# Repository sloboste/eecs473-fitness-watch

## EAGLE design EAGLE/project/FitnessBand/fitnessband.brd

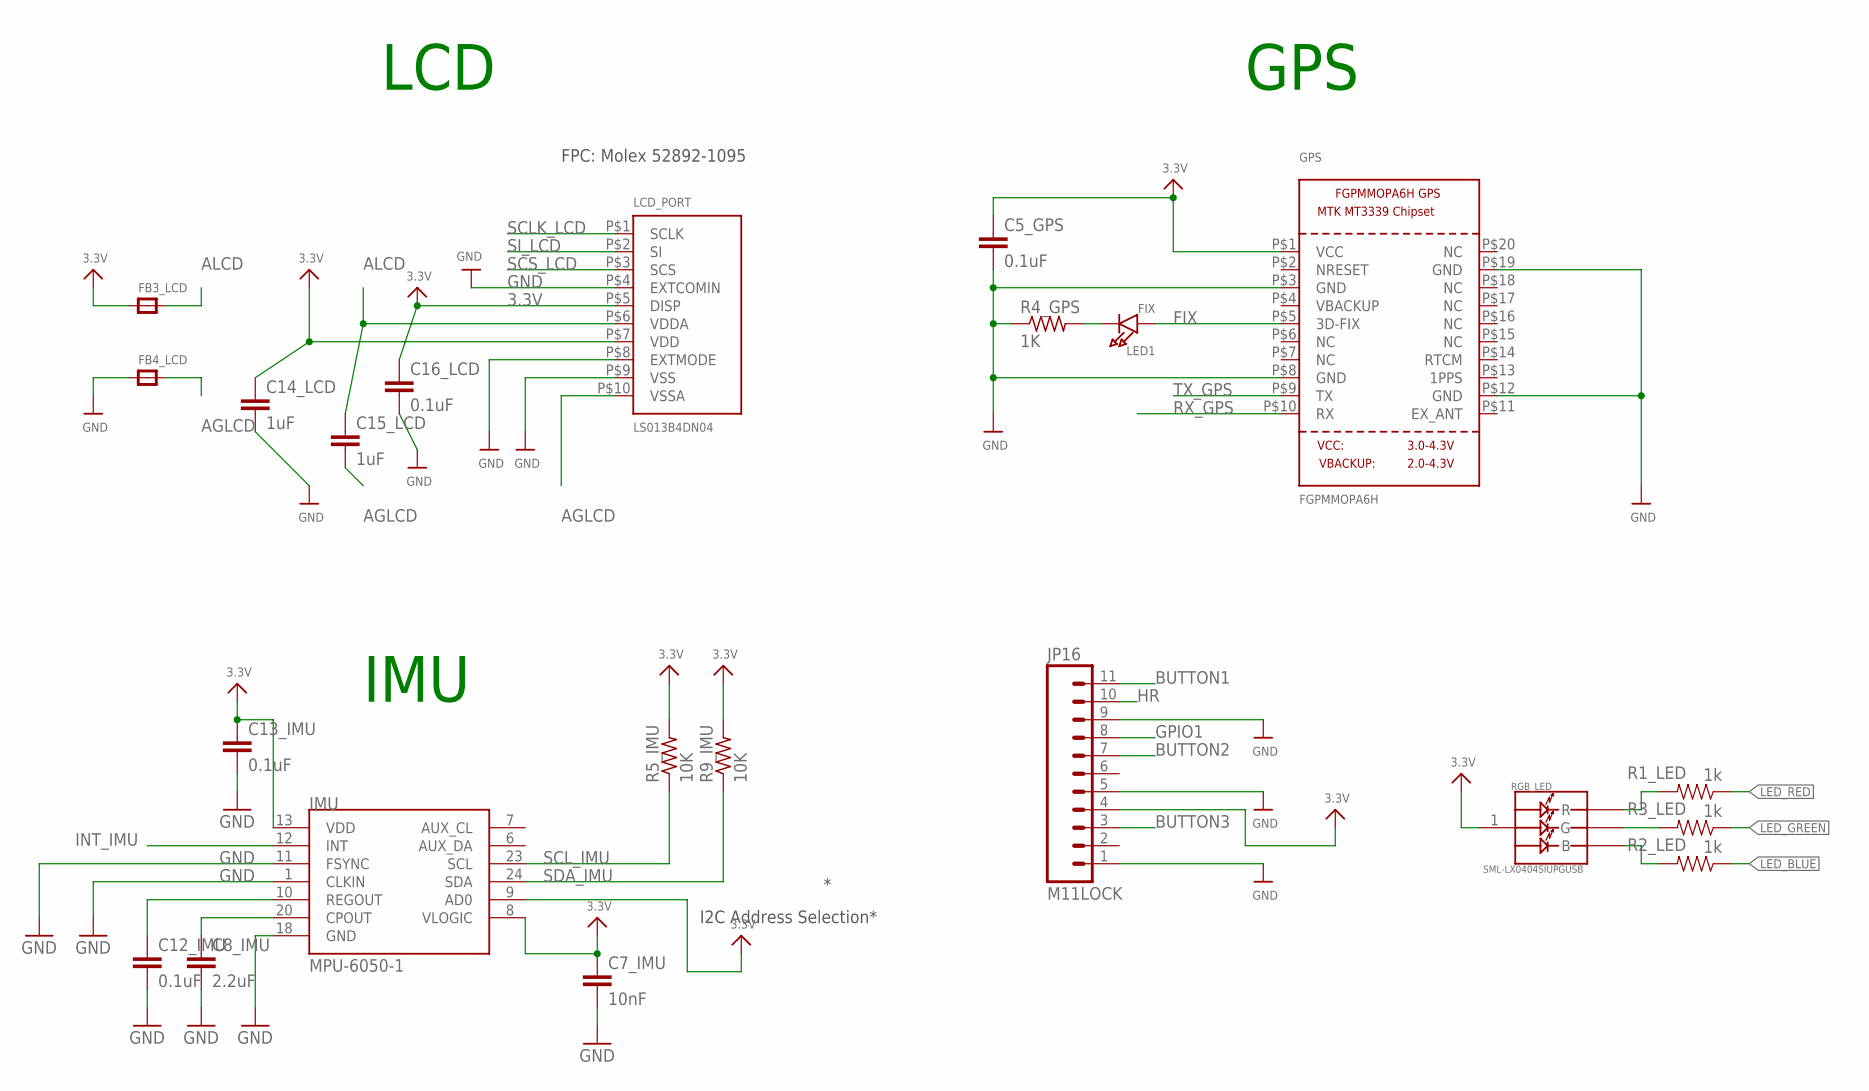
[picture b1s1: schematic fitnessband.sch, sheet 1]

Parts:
C5_GPS, C12_IMU, C13_IMU, C16_LCD: 0.1uF; C0402
C7_IMU: 10nF; C0402
C8_IMU: 2.2uF; C0402
C14_LCD, C15_LCD: 1uF; C0402
FB3_LCD, FB4_LCD: FERRITE_0805; _0805
GPS: FGPMMOPA6H
IMU: MPU-6050-1; QFN-24-4MM2
JP16: M11LOCK; 1X11_LOCK
LCD_PORT: LS013B4DN04; FPC_10PIN_52892-1095
LED1: FIX; CHIPLED_0805
R1_LED, R2_LED, R3_LED: 1k; 0402_RES
R4_GPS: 1K; R0402
R5_IMU, R9_IMU: 10K; R0402
RGB_LED: SML-LX0404SIUPGUSB; 1MM_SQ_4PAD

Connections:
3.3V: C5_GPS.1, C7_IMU.1, C13_IMU.1, C14_LCD.1, C16_LCD.1, FB3_LCD.1, GPS.P$1 (VCC), IMU.8 (VLOGIC), IMU.9 (AD0), IMU.13 (VDD), JP16.4, LCD_PORT.P$5 (DISP), LCD_PORT.P$7 (VDD), R5_IMU.2, R9_IMU.2, RGB_LED.1 (VDD); also elsewhere on the board
AGLCD: C15_LCD.2, FB4_LCD.2, LCD_PORT.P$10 (VSSA)
ALCD: C15_LCD.1, FB3_LCD.2, LCD_PORT.P$6 (VDDA)
BUTTON1: JP16.11; also elsewhere on the board
BUTTON2: JP16.7; also elsewhere on the board
BUTTON3: JP16.3; also elsewhere on the board
FIX: GPS.P$5 (3D-FIX), LED1.A
GND: C5_GPS.2, C7_IMU.2, C8_IMU.2, C12_IMU.2, C13_IMU.2, C14_LCD.2, C16_LCD.2, FB4_LCD.1, GPS.P$3 (GND), GPS.P$8 (GND), GPS.P$12 (GND), GPS.P$19 (GND), IMU.1 (CLKIN), IMU.11 (FSYNC), IMU.18 (GND), JP16.1, JP16.5, JP16.9, LCD_PORT.P$4 (EXTCOMIN), LCD_PORT.P$8 (EXTMODE), LCD_PORT.P$9 (VSS), R4_GPS.1; also elsewhere on the board
GPIO1: JP16.8; also elsewhere on the board
HR: JP16.10; also elsewhere on the board
INT_IMU: IMU.12 (INT); also elsewhere on the board
LED_BLUE: R2_LED.1; also elsewhere on the board
LED_GREEN: R3_LED.1; also elsewhere on the board
LED_RED: R1_LED.1; also elsewhere on the board
unnamed: R1_LED.2, RGB_LED.2 (R)
unnamed: R3_LED.2, RGB_LED.4 (G)
unnamed: R2_LED.2, RGB_LED.3 (B)
unnamed: LED1.C, R4_GPS.2
unnamed: C8_IMU.1, IMU.20 (CPOUT)
unnamed: C12_IMU.1, IMU.10 (REGOUT)
RX_GPS: GPS.P$10 (RX); also elsewhere on the board
SCLK_LCD: LCD_PORT.P$1 (SCLK); also elsewhere on the board
SCL_IMU: IMU.23 (SCL), R5_IMU.1; also elsewhere on the board
SCS_LCD: LCD_PORT.P$3 (SCS); also elsewhere on the board
SDA_IMU: IMU.24 (SDA), R9_IMU.1; also elsewhere on the board
SI_LCD: LCD_PORT.P$2 (SI); also elsewhere on the board
TX_GPS: GPS.P$9 (TX); also elsewhere on the board

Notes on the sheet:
FPC: Molex 52892-1095
LCD
GPS
I2C Address Selection*
IMU

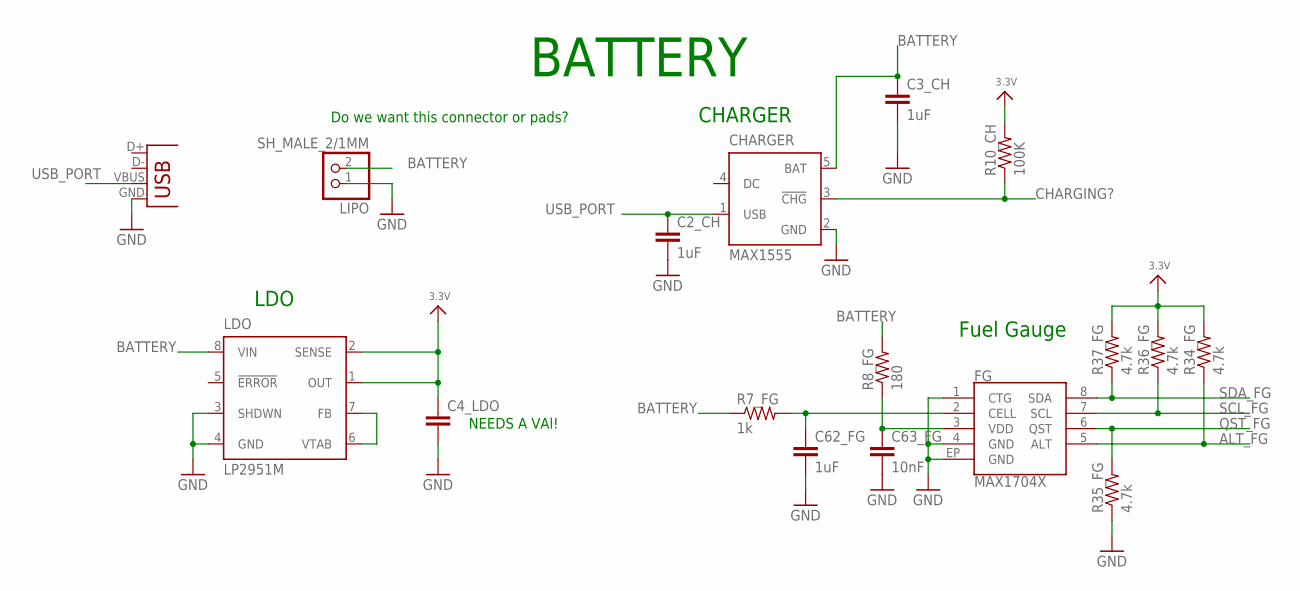
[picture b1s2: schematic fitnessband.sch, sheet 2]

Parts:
C2_CH, C3_CH: 1uF; C0402
C4_LDO: C-EUC0402; C0402
C62_FG: 1uF; 0402-CAP
C63_FG: 10nF; 0402-CAP
CHARGER: MAX1555; SOT23-5L
FG: MAX1704X; TDFN-8
LDO: LP2951M; SO08
LIPO: SH_MALE_2/1MM; SH-1X2/1MM
R7_FG: 1k; 0402-RES
R8_FG: 180; 0402-RES
R10_CH: 100K; R0402
R34_FG, R35_FG, R36_FG, R37_FG: 4.7k; 0402-RES
X5: USB-MICROB

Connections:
3.3V: C4_LDO.1, LDO.1 (OUT), LDO.2 (SENSE), R10_CH.2, R34_FG.2, R36_FG.2, R37_FG.2; also elsewhere on the board
ALT_FG: FG.5 (ALT), R34_FG.1; also elsewhere on the board
BATTERY: C3_CH.1, CHARGER.5 (BAT), LDO.8 (VIN), LIPO.2, R7_FG.1, R8_FG.2
CHARGING?: CHARGER.3 (!CHG), R10_CH.1; also elsewhere on the board
GND: C2_CH.2, C3_CH.2, C4_LDO.2, C62_FG.2, C63_FG.2, CHARGER.2 (GND), FG.1 (CTG), FG.4 (GND), FG.EP (GND), LDO.3 (SHDWN), LDO.4 (GND), LIPO.1, R35_FG.1, X5.GND; also elsewhere on the board
unnamed: LDO.6 (VTAB), LDO.7 (FB)
unnamed: C62_FG.1, FG.2 (CELL), R7_FG.2
QST_FG: FG.6 (QST), R35_FG.2; also elsewhere on the board
SCL_FG: FG.7 (SCL), R36_FG.1; also elsewhere on the board
SDA_FG: FG.8 (SDA), R37_FG.1; also elsewhere on the board
USB_PORT: C2_CH.1, CHARGER.1 (USB), X5.VBUS
VDD: C63_FG.1, FG.3 (VDD), R8_FG.1

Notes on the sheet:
Do we want this connector or pads?
BATTERY
LDO
CHARGER
NEEDS A VAl!
Fuel Gauge

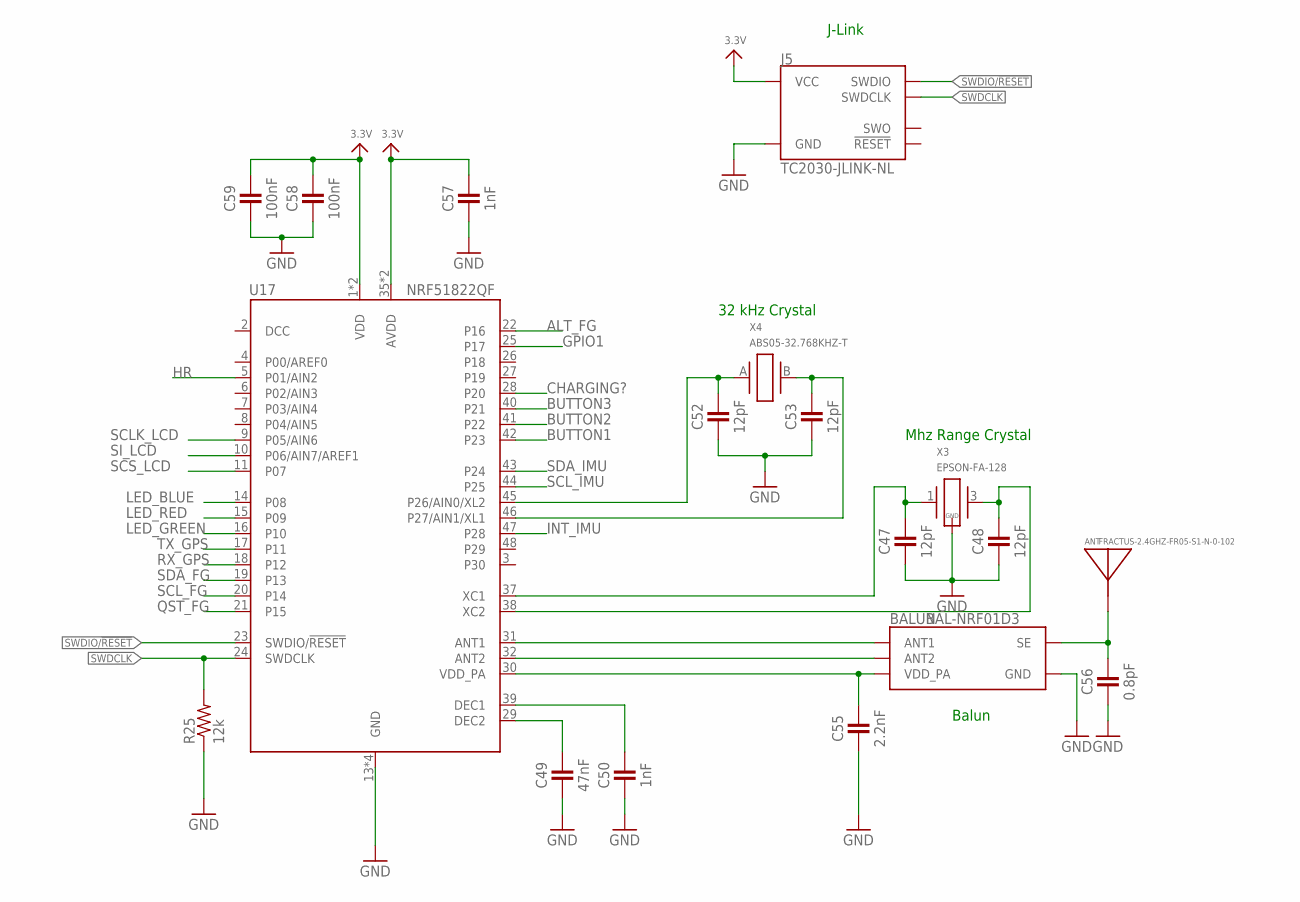
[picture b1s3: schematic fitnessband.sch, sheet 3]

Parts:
ANT: FRACTUS-2.4GHZ-FR05-S1-N-0-102; FRACTUS-ANTENNA-FR05-S1-N-0-102
BALUN: BAL-NRF01D3
C47, C48, C52, C53: 12pF; 0402_CAP
C49: 47nF; 0402_CAP
C50, C57: 1nF; 0402_CAP
C55: 2.2nF; 0402_CAP
C56: 0.8pF; 0402_CAP
C58, C59: 100nF; 0402_CAP
J5: TC2030-JLINK-NL; TC2030-IDC-NL
R25: 12k; 0402_RES
U17: NRF51822QF; QFN-48-6MM
X3: EPSON-FA-128; FA-128
X4: ABS05-32.768KHZ-T; ABS05

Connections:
3.3V: C57.1, C58.1, C59.1, J5.1 (VCC), U17.1 (VDD), U17.12 (VDD), U17.35 (AVDD), U17.36 (AVDD); also elsewhere on the board
ALT_FG: U17.22 (P16); also elsewhere on the board
ANTENNA1: ANT.1, BALUN.SE, C56.1
BUTTON1: U17.42 (P23); also elsewhere on the board
BUTTON2: U17.41 (P22); also elsewhere on the board
BUTTON3: U17.40 (P21); also elsewhere on the board
CHARGING?: U17.28 (P20); also elsewhere on the board
GND: BALUN.GND, C47.2, C48.2, C49.2, C50.2, C52.2, C53.2, C55.2, C56.2, C57.2, C58.2, C59.2, J5.5 (GND), R25.1, U17.13 (GND), U17.33 (GND), U17.34 (GND), U17.GND, X3.2 (GND), X3.4 (GND); also elsewhere on the board
GPIO1: U17.25 (P17); also elsewhere on the board
HR: U17.5 (P01/AIN2); also elsewhere on the board
INT_IMU: U17.47 (P28); also elsewhere on the board
LED_BLUE: U17.14 (P08); also elsewhere on the board
LED_GREEN: U17.16 (P10); also elsewhere on the board
LED_RED: U17.15 (P09); also elsewhere on the board
unnamed: C47.1, U17.37 (XC1), X3.1
unnamed: C48.1, U17.38 (XC2), X3.3 (2)
unnamed: C49.1, U17.29 (DEC2)
unnamed: C52.1, U17.45 (P26/AIN0/XL2), X4.A (1)
unnamed: C53.1, U17.46 (P27/AIN1/XL1), X4.B (2)
unnamed: C50.1, U17.39 (DEC1)
unnamed: BALUN.ANT1, U17.31 (ANT1)
unnamed: BALUN.ANT2, U17.32 (ANT2)
unnamed: BALUN.VCC (VDD_PA), C55.1, U17.30 (VDD_PA)
QST_FG: U17.21 (P15); also elsewhere on the board
RX_GPS: U17.18 (P12); also elsewhere on the board
SCLK_LCD: U17.9 (P05/AIN6); also elsewhere on the board
SCL_FG: U17.20 (P14); also elsewhere on the board
SCL_IMU: U17.44 (P25); also elsewhere on the board
SCS_LCD: U17.11 (P07); also elsewhere on the board
SDA_FG: U17.19 (P13); also elsewhere on the board
SDA_IMU: U17.43 (P24); also elsewhere on the board
SI_LCD: U17.10 (P06/AIN7/AREF1); also elsewhere on the board
SWDCLK: J5.4 (SWDCLK), R25.2, U17.24 (SWDCLK)
SWDIO/!RESET: J5.2 (SWDIO), U17.23 (SWDIO/!RESET)
TX_GPS: U17.17 (P11); also elsewhere on the board

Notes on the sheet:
J-Link
Balun
Mhz Range Crystal
32 kHz Crystal

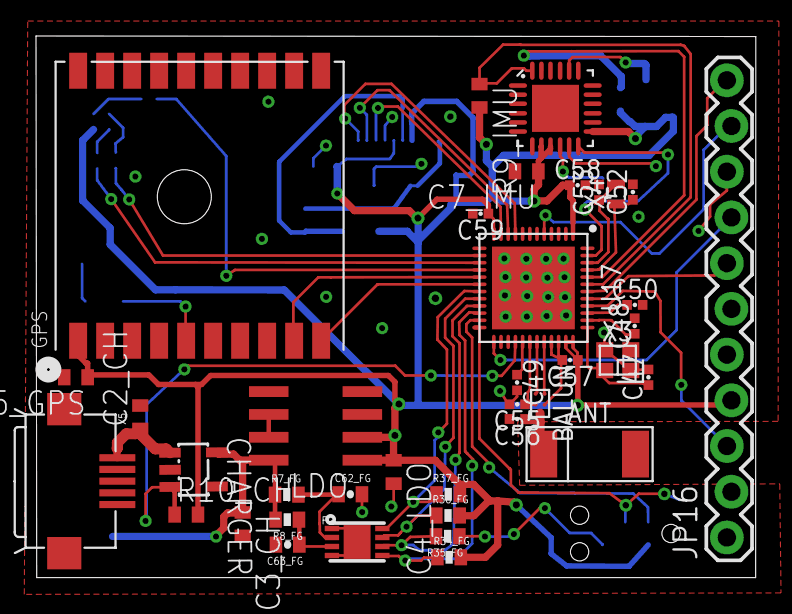
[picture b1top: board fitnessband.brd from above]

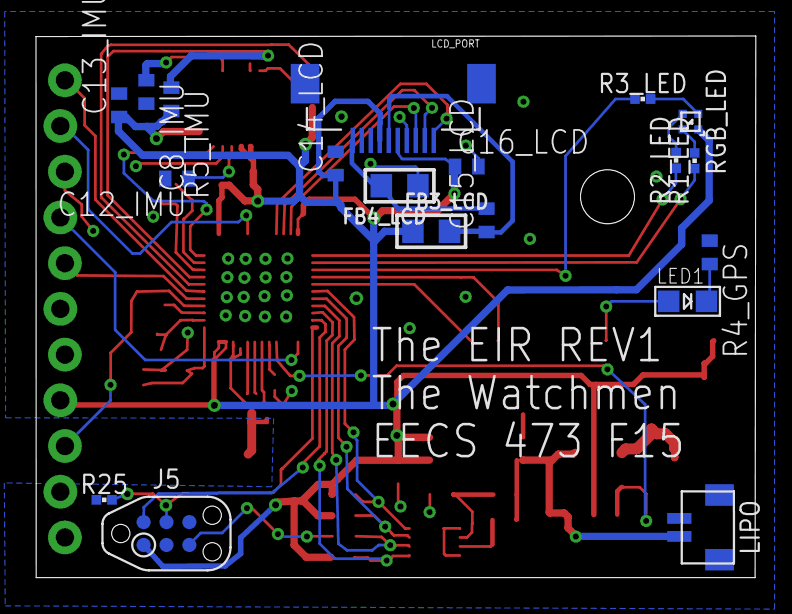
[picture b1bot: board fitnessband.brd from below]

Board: 2 copper layers, 40.0 x 30.1 mm, 57 parts (19 on the bottom side), 49 nets.

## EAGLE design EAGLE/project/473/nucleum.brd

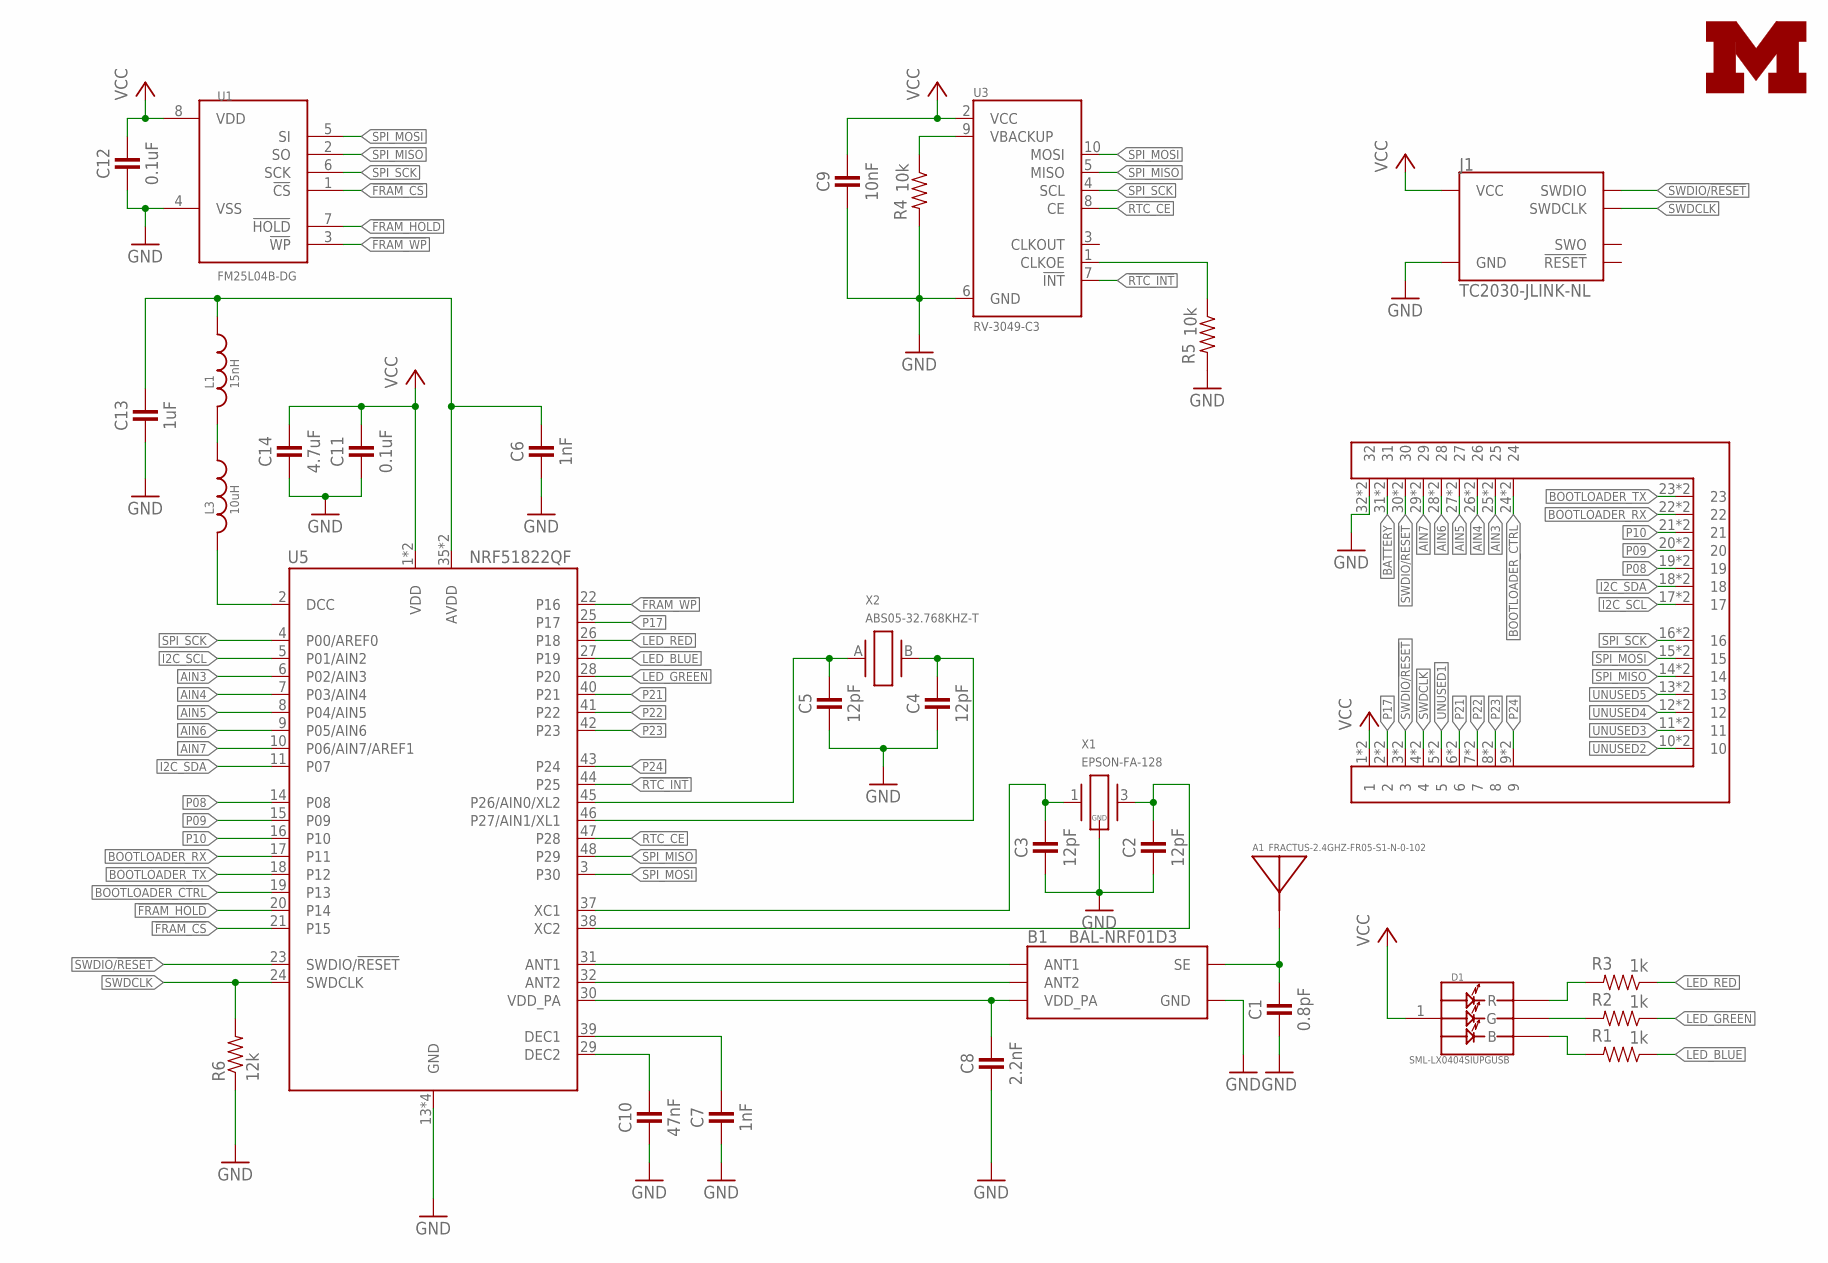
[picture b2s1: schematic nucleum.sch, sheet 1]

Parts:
A1: FRACTUS-2.4GHZ-FR05-S1-N-0-102; FRACTUS-ANTENNA-FR05-S1-N-0-102
B1: BAL-NRF01D3
C1: 0.8pF; 0402_CAP
C2, C3, C4, C5: 12pF; 0402_CAP
C6, C7: 1nF; 0402_CAP
C8: 2.2nF; 0402_CAP
C9: 10nF; 0402_CAP
C10: 47nF; 0402_CAP
C11, C12: 0.1uF; 0402_CAP
C13: 1uF; 0402_CAP
C14: 4.7uF; 0402_CAP
D1: SML-LX0404SIUPGUSB; 1MM_SQ_4PAD
J1: TC2030-JLINK-NL; TC2030-IDC-NL
J3: ATUM-HEADER
L1: 15nH; 0402_CAP
L3: 10uH; 0603_CAP
LOGO1: UMICH_SOLID_TINY; UMICH_SOLID_50MIL
R1, R2, R3: 1k; 0402_RES
R4, R5: 10k; 0402_RES
R6: 12k; 0402_RES
U1: FM25L04B-DG; TDFN-8
U3: RV-3049-C3; MICRO-CRYSTAL-C3
U5: NRF51822QF; QFN-48-6MM
X1: EPSON-FA-128; FA-128
X2: ABS05-32.768KHZ-T; ABS05

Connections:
!FRAM_CS: U1.1 (!CS), U5.21 (P15)
!FRAM_HOLD: U1.7 (!HOLD), U5.20 (P14)
!FRAM_WP: U1.3 (!WP), U5.22 (P16)
!RTC_INT: U3.7 (!INT), U5.44 (P25)
AIN3: J3.25, J3.25B (25), U5.6 (P02/AIN3)
AIN4: J3.26, J3.26B (26), U5.7 (P03/AIN4)
AIN5: J3.27, J3.27B (27), U5.8 (P04/AIN5)
AIN6: J3.28, J3.28B (28), U5.9 (P05/AIN6)
AIN7: J3.29, J3.29B (29), U5.10 (P06/AIN7/AREF1)
ANTENNA: A1.1, B1.SE, C1.1
BATTERY: J3.31, J3.31B (31); also elsewhere on the board
BOOTLOADER_CTRL: J3.24, J3.24B (24), U5.19 (P13)
BOOTLOADER_RX: J3.22, J3.22B (22), U5.17 (P11)
BOOTLOADER_TX: J3.23, J3.23B (23), U5.18 (P12)
GND: B1.GND, C1.2, C2.2, C3.2, C4.2, C5.2, C6.2, C7.2, C8.2, C9.2, C10.2, C11.2, C12.2, C13.2, C14.2, J1.5 (GND), J3.32, J3.32B (32), R4.2, R5.2, R6.1, U1.4 (VSS), U3.6 (GND), U5.13 (GND), U5.33 (GND), U5.34 (GND), U5.GND, X1.2 (GND), X1.4 (GND); also elsewhere on the board
I2C_SCL: J3.17, J3.17B (17), U5.5 (P01/AIN2)
I2C_SDA: J3.18, J3.18B (18), U5.11 (P07)
LED_BLUE: R1.1, U5.27 (P19)
LED_GREEN: R2.1, U5.28 (P20)
LED_RED: R3.1, U5.26 (P18)
unnamed: C5.1, U5.45 (P26/AIN0/XL2), X2.A (1)
unnamed: D1.2 (R), R3.2
unnamed: C3.1, U5.37 (XC1), X1.1
unnamed: C2.1, U5.38 (XC2), X1.3 (2)
unnamed: D1.4 (G), R2.2
unnamed: D1.3 (B), R1.2
unnamed: C4.1, U5.46 (P27/AIN1/XL1), X2.B (2)
unnamed: R4.1, U3.9 (VBACKUP)
unnamed: C10.1, U5.29 (DEC2)
unnamed: R5.1, U3.1 (CLKOE)
unnamed: C7.1, U5.39 (DEC1)
unnamed: B1.ANT1, U5.31 (ANT1)
unnamed: B1.ANT2, U5.32 (ANT2)
unnamed: B1.VCC (VDD_PA), C8.1, U5.30 (VDD_PA)
unnamed: C6.1, C13.1, L1.1, U5.35 (AVDD), U5.36 (AVDD)
unnamed: L1.2, L3.1
unnamed: L3.2, U5.2 (DCC)
P08: J3.19, J3.19B (19), U5.14 (P08)
P09: J3.20, J3.20B (20), U5.15 (P09)
P10: J3.21, J3.21B (21), U5.16 (P10)
P17: J3.2, J3.2B (2), U5.25 (P17)
P21: J3.6, J3.6B (6), U5.40 (P21)
P22: J3.7, J3.7B (7), U5.41 (P22)
P23: J3.8, J3.8B (8), U5.42 (P23)
P24: J3.9, J3.9B (9), U5.43 (P24)
RTC_CE: U3.8 (CE), U5.47 (P28)
SPI_MISO: J3.14, J3.14B (14), U1.2 (SO), U3.5 (MISO), U5.48 (P29)
SPI_MOSI: J3.15, J3.15B (15), U1.5 (SI), U3.10 (MOSI), U5.3 (P30)
SPI_SCK: J3.16, J3.16B (16), U1.6 (SCK), U3.4 (SCL), U5.4 (P00/AREF0)
SWDCLK: J1.4 (SWDCLK), J3.4, J3.4B (4), R6.2, U5.24 (SWDCLK)
SWDIO/!RESET: J1.2 (SWDIO), J3.3, J3.3B (3), J3.30, J3.30B (30), U5.23 (SWDIO/!RESET)
UNUSED1: J3.5, J3.5B (5)
UNUSED2: J3.10, J3.10B (10)
UNUSED3: J3.11, J3.11B (11)
UNUSED4: J3.12, J3.12B (12)
UNUSED5: J3.13, J3.13B (13)
VCC: C9.1, C11.1, C12.1, C14.1, D1.1 (VDD), J1.1 (VCC), J3.1, J3.1B (1), U1.8 (VDD), U3.2 (VCC), U5.1 (VDD), U5.12 (VDD); also elsewhere on the board

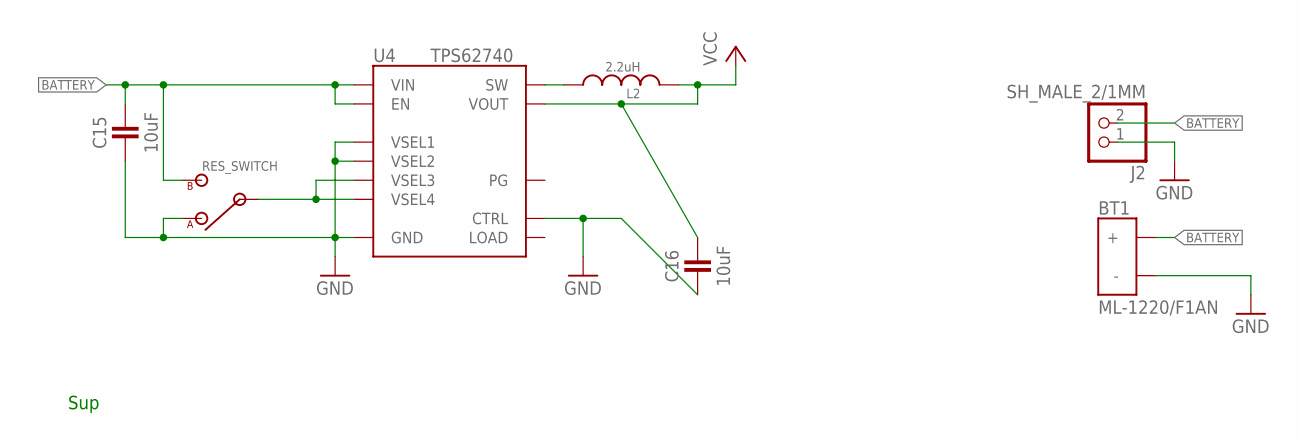
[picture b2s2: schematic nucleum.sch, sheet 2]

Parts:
BT1: ML-1220/F1AN; ML-1220/F1BN
C15, C16: 10uF; 0603_CAP; DIGIKEY 490-7316-1-ND
J2: SH_MALE_2/1MM; SH-1X2/1MM
L2: 2.2uH; MIPSZ201D
S1: RES_SWITCH
U4: TPS62740; R-PWSON-12

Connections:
BATTERY: BT1.POS (+), C15.1, J2.2, S1.B, U4.1 (VIN), U4.12 (EN); also elsewhere on the board
GND: BT1.NEG (-), C15.2, C16.2, J2.1, S1.A, U4.3 (GND), U4.4 (CTRL), U4.10 (VSEL2), U4.11 (VSEL1), U4.NC (GND); also elsewhere on the board
unnamed: L2.1, U4.2 (SW)
unnamed: S1.C (IN), U4.8 (VSEL4), U4.9 (VSEL3)
VCC: C16.1, L2.2, U4.5 (VOUT); also elsewhere on the board

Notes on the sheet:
Sup

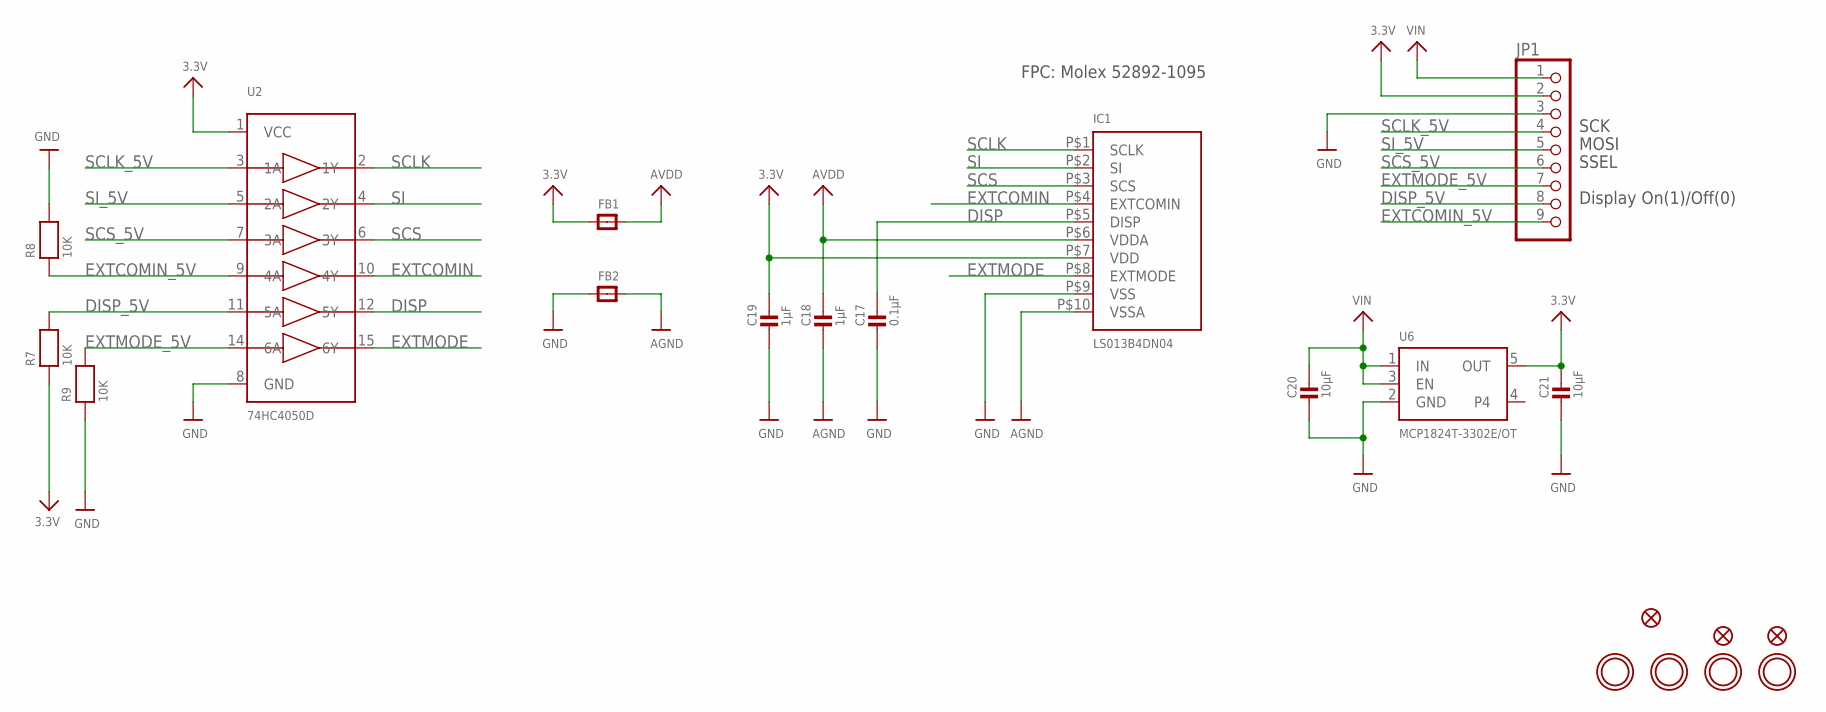
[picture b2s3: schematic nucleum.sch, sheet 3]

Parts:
C17: 0.1µF; _0805
C18, C19: 1µF; _0805
C20, C21: 10µF; _0805
FB1, FB2: FERRITE_0805; _0805
FID1, FID2, FID3: FIDUCIAL""; FIDUCIAL_1MM
IC1: LS013B4DN04; FPC_10PIN_52892-1095
JP1: HEADER-1X970MIL; 1X09_ROUND_70
R7, R8, R9: 10K; _0805
U2: 74HC4050D; SOIC16
U6: MCP1824T-3302E/OT; SOT23-5
U$21, U$22, U$27, U$28: MOUNTINGHOLE3.0THIN; MOUNTINGHOLE_3.0_PLATEDTHIN

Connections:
3.3V: C19.1, C21.1, FB1.1, IC1.P$7 (VDD), JP1.2, R7.1, U2.1 (VCC), U6.5 (OUT)
AGND: C18.2, FB2.2, IC1.P$10 (VSSA)
AVDD: C18.1, FB1.2, IC1.P$6 (VDDA)
DISP: C17.1, IC1.P$5 (DISP), U2.12 (5Y)
DISP_5V: JP1.8, R7.2, U2.11 (5A)
EXTCOMIN: IC1.P$4 (EXTCOMIN), U2.10 (4Y)
EXTCOMIN_5V: JP1.9, R8.1, U2.9 (4A)
EXTMODE: IC1.P$8 (EXTMODE), U2.15 (6Y)
EXTMODE_5V: JP1.7, R9.2, U2.14 (6A)
GND: C17.2, C19.2, C20.2, C21.2, FB2.1, IC1.P$9 (VSS), JP1.3, R8.2, R9.1, U2.8 (GND), U6.2 (GND); also elsewhere on the board
SCLK: IC1.P$1 (SCLK), U2.2 (1Y)
SCLK_5V: JP1.4, U2.3 (1A)
SCS: IC1.P$3 (SCS), U2.6 (3Y)
SCS_5V: JP1.6, U2.7 (3A)
SI: IC1.P$2 (SI), U2.4 (2Y)
SI_5V: JP1.5, U2.5 (2A)
VIN: C20.1, JP1.1, U6.1 (IN), U6.3 (EN)

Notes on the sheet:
SSEL
MOSI
SCK
Display On(1)/Off(0)
FPC: Molex 52892-1095

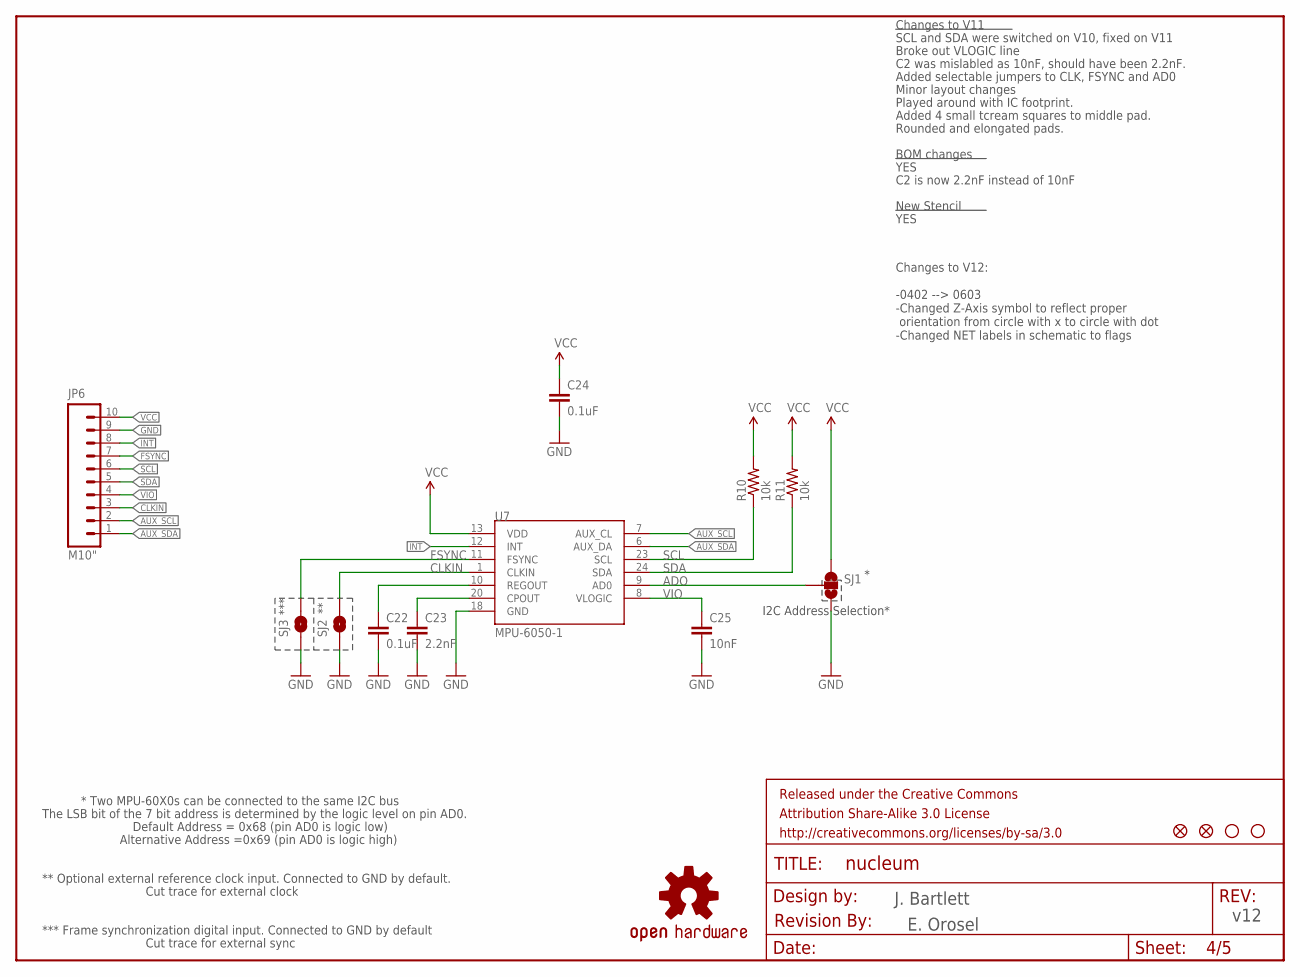
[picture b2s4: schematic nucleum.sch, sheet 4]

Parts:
C22, C24: 0.1uF; 0603-CAP
C23: 2.2nF; 0603-CAP
C25: 10nF; 0603-CAP
FRAME4: FRAME-LETTER; CREATIVE_COMMONS
JP2, JP5: FIDUCIALUFIDUCIAL; MICRO-FIDUCIAL
JP3, JP4: STAND-OFFTIGHT; STAND-OFF-TIGHT
JP6: M10"; 1X10
R10, R11: 10k; 0603-RES
SJ1: SOLDERJUMPER_2WAYPASTE2&3; SJ_3_PASTE2&3
SJ2, SJ3: SOLDERJUMPERTRACE; SJ_2S-TRACE
U7: MPU-6050-1; QFN-24-4MM2
U$30: OSHW-LOGOS; OSHW-LOGO-S
U$31: REVISION

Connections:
ADO: SJ1.2, U7.9 (AD0)
AUX_SCL: JP6.2, U7.7 (AUX_CL)
AUX_SDA: JP6.1, U7.6 (AUX_DA)
CLKIN: JP6.3, SJ2.2, U7.1 (CLKIN)
FSYNC: JP6.7, SJ3.2, U7.11 (FSYNC)
GND: C22.2, C23.2, C24.2, C25.2, JP6.9, SJ1.3, SJ2.1, SJ3.1, U7.18 (GND); also elsewhere on the board
INT: JP6.8, U7.12 (INT)
unnamed: C23.1, U7.20 (CPOUT)
unnamed: C22.1, U7.10 (REGOUT)
SCL: JP6.6, R10.1, U7.23 (SCL)
SDA: JP6.5, R11.1, U7.24 (SDA)
VCC: C24.1, JP6.10, R10.2, R11.2, SJ1.1, U7.13 (VDD); also elsewhere on the board
VIO: C25.1, JP6.4, U7.8 (VLOGIC)

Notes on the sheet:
J. Bartlett
I2C Address Selection*
*** Frame synchronization digital input. Connected to GND by default
***
Cut trace for external sync
* Two MPU-60X0s can be connected to the same I2C bus
Default Address = 0x68 (pin AD0 is logic low)
Alternative Address =0x69 (pin AD0 is logic high)
The LSB bit of the 7 bit address is determined by the logic level on pin AD0.
** Optional external reference clock input. Connected to GND by default.
Cut trace for external clock
Changes to V11
SCL and SDA were switched on V10, fixed on V11
C2 was mislabled as 10nF, should have been 2.2nF.
Broke out VLOGIC line
BOM changes
New Stencil
YES
C2 is now 2.2nF instead of 10nF
Minor layout changes
Added selectable jumpers to CLK, FSYNC and AD0
Played around with IC footprint.
Changes to V12: -0402 --> 0603 -Changed Z-Axis symbol to reflect proper orientation from circle with x to circle with dot -Changed NET labels in schematic to flags
E. Orosel
v12
Added 4 small tcream squares to middle pad.
Rounded and elongated pads.

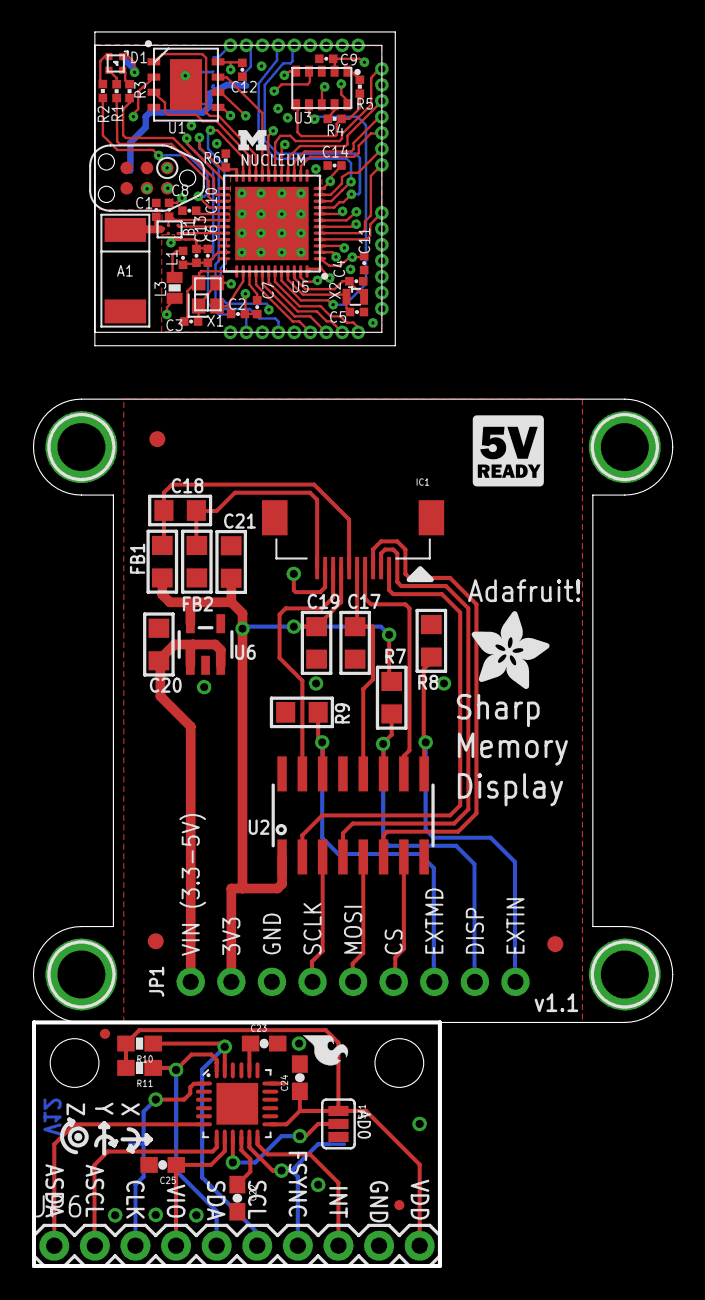
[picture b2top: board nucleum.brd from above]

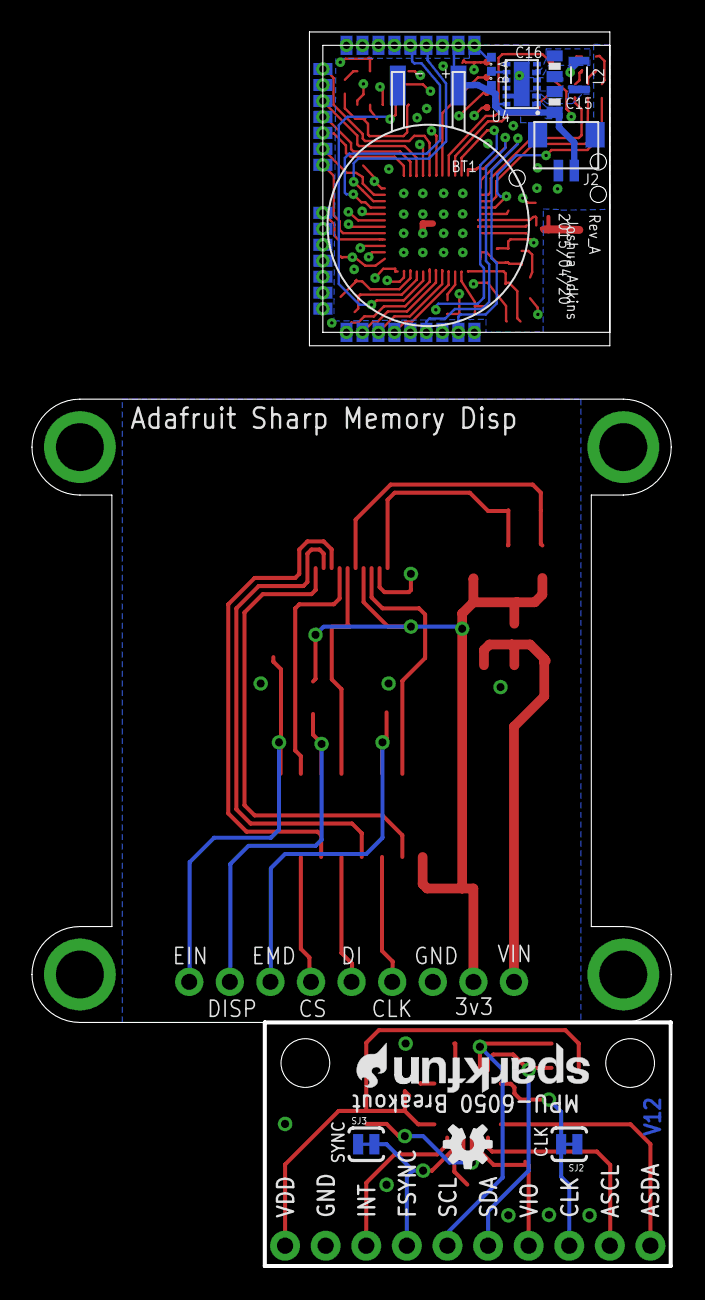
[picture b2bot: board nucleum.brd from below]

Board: 4 copper layers, 39.8 x 77.1 mm, 84 parts (12 on the bottom side), 86 nets.

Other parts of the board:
U$19: LOGIC_5VREADY_5MM
U$29: ADAFRUIT_5MM
U$32, U$33: SFE-LOGO-FLAME
U$34: SFE-NEW-WEB

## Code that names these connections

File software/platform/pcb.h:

/* Pin assignemnts on the custom PCB.
 * 
 * TODO fix the pin assignments
 */

#ifndef PCB_H
#define PCB_H

// Push button switches
#define PIN_BUTTON_1 23
#define PIN_BUTTON_2 22 
#define PIN_BUTTON_3 21

#define BUTTON_PULL GPIO_PIN_CNF_PULL_Pullup

// LEDs
#define PIN_LED_1 8
#define PIN_LED_2 9
#define PIN_LED_3 10

// UART
#define PIN_RTS 2 
#define PIN_TXD 12
#define PIN_CTS 3
#define PIN_RXD 11

// SPI
#define SPI_SCK_PIN  5                                                          
#define SPI_MISO_PIN 6                                                         
#define SPI_MOSI_PIN 0 // Not connected                                                         
#define SPI_SS_PIN   7 
#define NRF_SPI NRF_SPI0 // TODO should we have an include for this?

// SW I2C / Fuel gauge
#define PIN_SW_I2C_SDA  13
#define PIN_SW_I2C_SCL  14
#define PIN_FUEL_QST    15

// HW I2C
// TODO

#endif

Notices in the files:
parts and their libraries:
SparkFun-Aesthetics: Licensing: CC v3.0 Share-Alike You are welcome to use this library for commercial purposes.
SparkFun-Aesthetics: Released under the Creative Commons Attribution Share-Alike 3.0 License
SparkFun-Aesthetics: http://creativecommons.org/licenses/by-sa/3.0
